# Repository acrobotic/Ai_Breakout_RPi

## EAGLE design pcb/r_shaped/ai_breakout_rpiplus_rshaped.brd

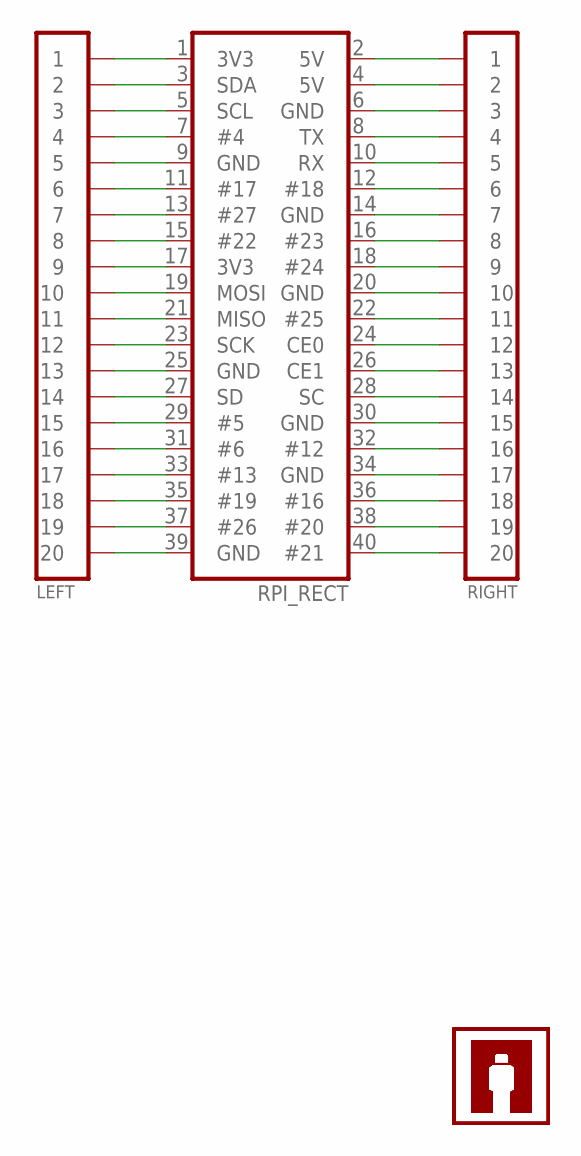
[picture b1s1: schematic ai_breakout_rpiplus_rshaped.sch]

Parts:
LEFT: 1X20
RIGHT: 1X20NOFIRST; 1X20-NOFIRST
RPI_RECT: 2X20-RPI-BRK
U$1, U$2: AI-LOGOXS; AI-LOGO-XS

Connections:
unnamed: LEFT.1, RPI_RECT.1 (3V3)
unnamed: LEFT.2, RPI_RECT.3 (SDA)
unnamed: LEFT.3, RPI_RECT.5 (SCL)
unnamed: LEFT.4, RPI_RECT.7 (#4)
unnamed: LEFT.5, RPI_RECT.9 (GND)
unnamed: LEFT.6, RPI_RECT.11 (#17)
unnamed: LEFT.7, RPI_RECT.13 (#27)
unnamed: LEFT.8, RPI_RECT.15 (#22)
unnamed: LEFT.9, RPI_RECT.17 (3V3)
unnamed: LEFT.10, RPI_RECT.19 (MOSI)
unnamed: LEFT.11, RPI_RECT.21 (MISO)
unnamed: LEFT.12, RPI_RECT.23 (SCK)
unnamed: LEFT.13, RPI_RECT.25 (GND)
unnamed: LEFT.14, RPI_RECT.27 (SD)
unnamed: LEFT.15, RPI_RECT.29 (#5)
unnamed: LEFT.16, RPI_RECT.31 (#6)
unnamed: LEFT.17, RPI_RECT.33 (#13)
unnamed: LEFT.18, RPI_RECT.35 (#19)
unnamed: LEFT.19, RPI_RECT.37 (#26)
unnamed: LEFT.20, RPI_RECT.39 (GND)
unnamed: RIGHT.20, RPI_RECT.40 (#21)
unnamed: RIGHT.19, RPI_RECT.38 (#20)
unnamed: RIGHT.18, RPI_RECT.36 (#16)
unnamed: RIGHT.17, RPI_RECT.34 (GND)
unnamed: RIGHT.16, RPI_RECT.32 (#12)
unnamed: RIGHT.15, RPI_RECT.30 (GND)
unnamed: RIGHT.14, RPI_RECT.28 (SC)
unnamed: RIGHT.13, RPI_RECT.26 (CE1)
unnamed: RIGHT.12, RPI_RECT.24 (CE0)
unnamed: RIGHT.11, RPI_RECT.22 (#25)
unnamed: RIGHT.10, RPI_RECT.20 (GND)
unnamed: RIGHT.9, RPI_RECT.18 (#24)
unnamed: RIGHT.8, RPI_RECT.16 (#23)
unnamed: RIGHT.7, RPI_RECT.14 (GND)
unnamed: RIGHT.6, RPI_RECT.12 (#18)
unnamed: RIGHT.5, RPI_RECT.10 (RX)
unnamed: RIGHT.4, RPI_RECT.8 (TX)
unnamed: RIGHT.3, RPI_RECT.6 (GND)
unnamed: RIGHT.2, RPI_RECT.4 (5V)
unnamed: RIGHT.1, RPI_RECT.2 (5V)

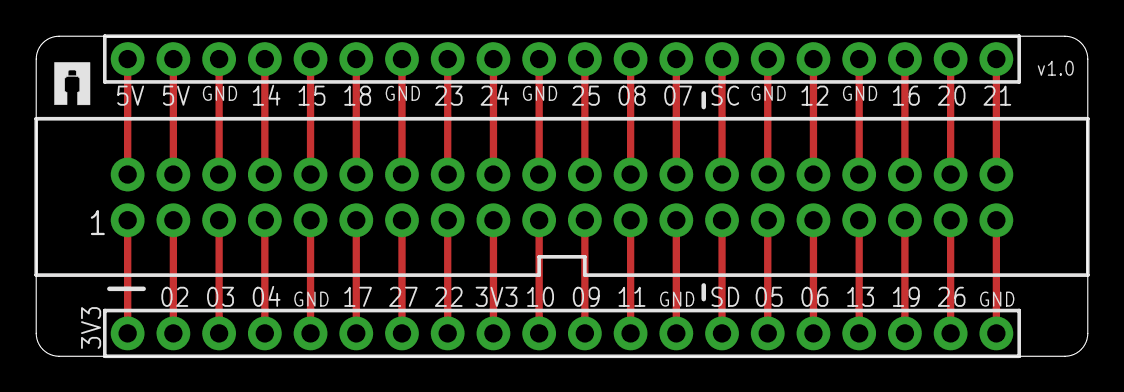
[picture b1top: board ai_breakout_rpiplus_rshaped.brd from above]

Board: 2 copper layers, 58.4 x 17.8 mm, 5 parts (1 on the bottom side), 40 nets.

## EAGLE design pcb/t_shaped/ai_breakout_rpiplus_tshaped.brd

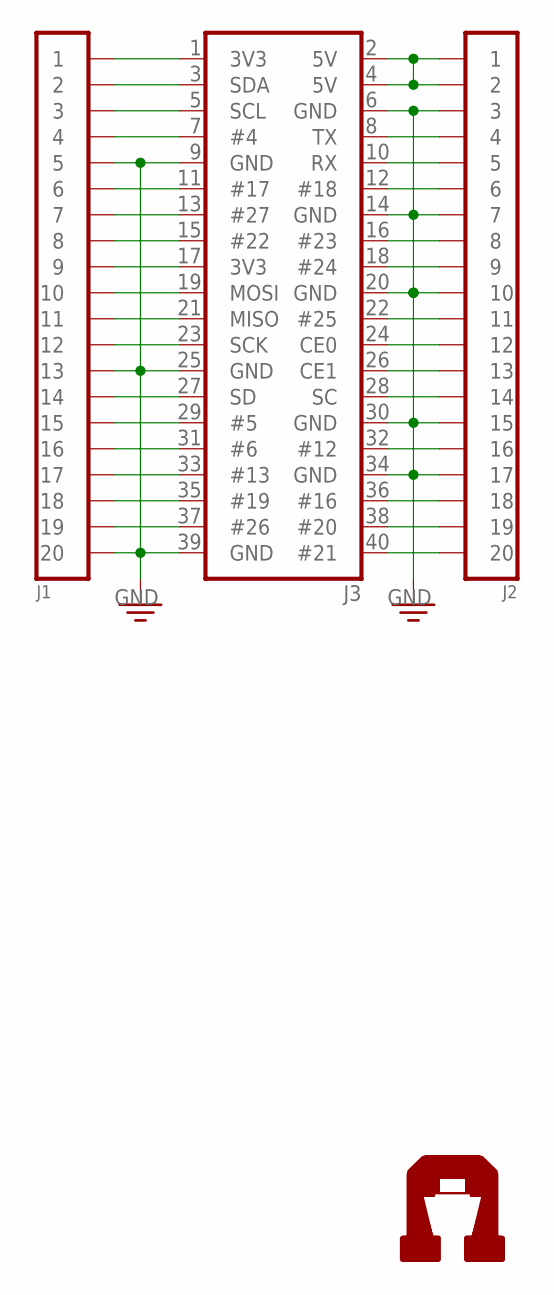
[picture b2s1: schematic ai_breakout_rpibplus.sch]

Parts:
J1: 1X20
J2: 1X20NOFIRST; 1X20-NOFIRST
J3: 2X20-RPI-BRK
U$1, U$2: AI-LOGOXS; AI-LOGO-XS

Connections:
GND: J1.5, J1.13, J1.20, J2.3, J2.7, J2.10, J2.15, J2.17, J3.6 (GND), J3.9 (GND), J3.14 (GND), J3.20 (GND), J3.25 (GND), J3.30 (GND), J3.34 (GND), J3.39 (GND)
unnamed: J2.1, J2.2, J3.2 (5V), J3.4 (5V)
unnamed: J1.19, J3.37 (#26)
unnamed: J1.18, J3.35 (#19)
unnamed: J1.17, J3.33 (#13)
unnamed: J1.16, J3.31 (#6)
unnamed: J1.15, J3.29 (#5)
unnamed: J1.14, J3.27 (SD)
unnamed: J1.12, J3.23 (SCK)
unnamed: J1.11, J3.21 (MISO)
unnamed: J1.10, J3.19 (MOSI)
unnamed: J1.9, J3.17 (3V3)
unnamed: J1.8, J3.15 (#22)
unnamed: J1.7, J3.13 (#27)
unnamed: J1.1, J3.1 (3V3)
unnamed: J1.2, J3.3 (SDA)
unnamed: J1.3, J3.5 (SCL)
unnamed: J1.4, J3.7 (#4)
unnamed: J1.6, J3.11 (#17)
unnamed: J2.8, J3.16 (#23)
unnamed: J2.16, J3.32 (#12)
unnamed: J2.4, J3.8 (TX)
unnamed: J2.5, J3.10 (RX)
unnamed: J2.6, J3.12 (#18)
unnamed: J2.9, J3.18 (#24)
unnamed: J2.11, J3.22 (#25)
unnamed: J2.12, J3.24 (CE0)
unnamed: J2.13, J3.26 (CE1)
unnamed: J2.14, J3.28 (SC)
unnamed: J2.18, J3.36 (#16)
unnamed: J2.19, J3.38 (#20)
unnamed: J2.20, J3.40 (#21)

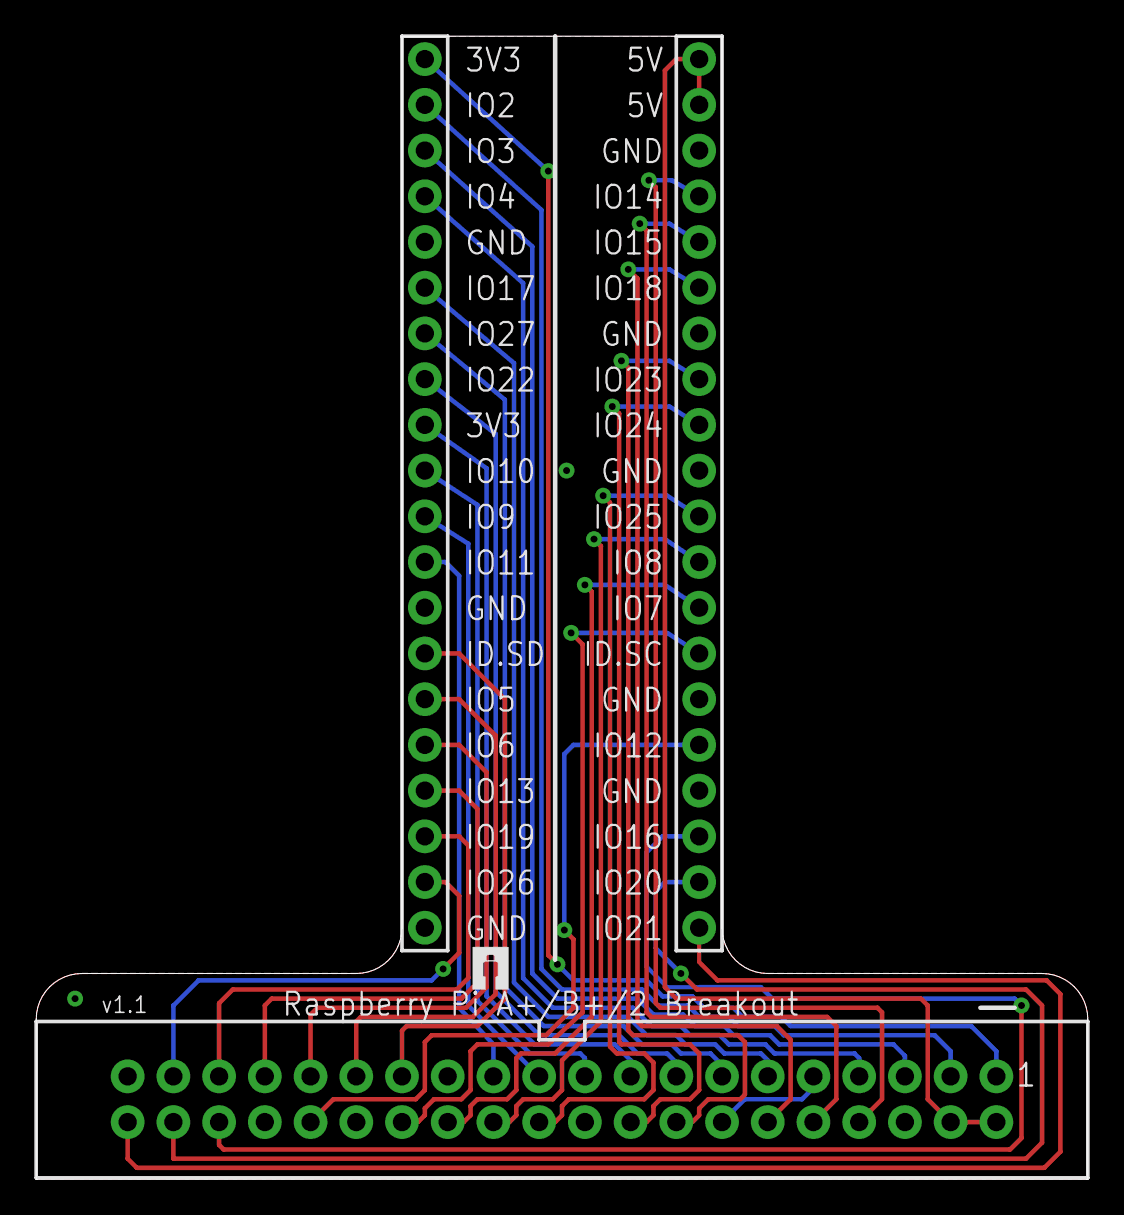
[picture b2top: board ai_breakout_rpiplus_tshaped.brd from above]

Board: 2 copper layers, 58.4 x 63.5 mm, 5 parts (1 on the bottom side), 32 nets.

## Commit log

2014-12-29 First commit.
2015-03-27 Gerber files generated for r-shaped
2015-04-16 Updating T-Shaped. Added a few labels to R-Shaped
2015-04-16 Renaming files
2015-04-25 updating
